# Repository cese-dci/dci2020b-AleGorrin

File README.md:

Prototipo Replica Adafruit HUZZAH32 - ESP32 Feather
TP Alejandro Gorrin
Diseno de Circuitos Impresos
11 Co Especializacion de sistemas embebidos

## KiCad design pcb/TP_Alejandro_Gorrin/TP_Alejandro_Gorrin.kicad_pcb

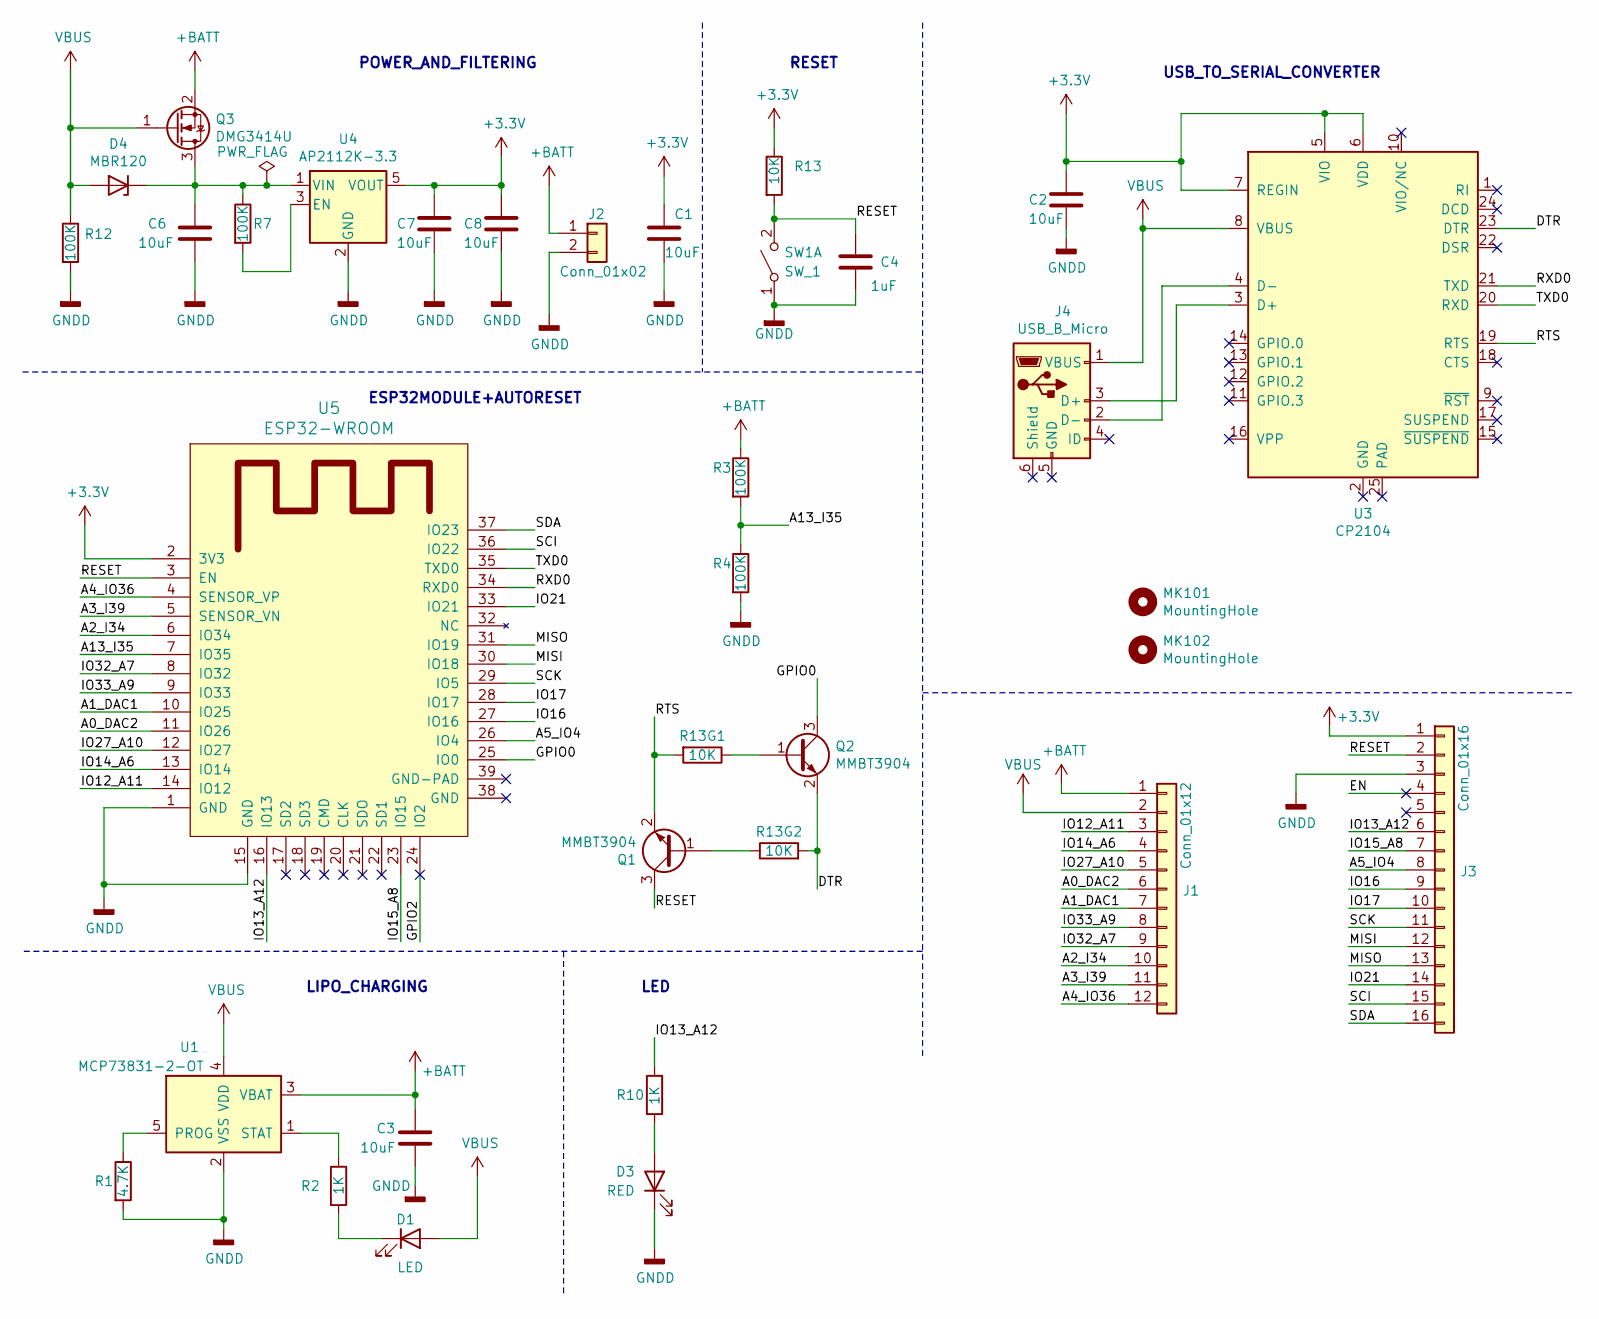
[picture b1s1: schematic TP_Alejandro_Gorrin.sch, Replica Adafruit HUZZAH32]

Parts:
C1, C2, C3, C6, C7, C8: 10uF; C_0805_2012Metric
C4: 1uF; C_0805_2012Metric
D1: LED; LED_0805_2012Metric
D3: RED; LED_0805_2012Metric
D4: MBR120; LED_0805_2012Metric
J1: Conn_01x12; PinHeader_1x12_P2.54mm_Vertical
J2: Conn_01x02; PinHeader_1x02_P2.54mm_Vertical
J3: Conn_01x16; PinHeader_1x16_P2.54mm_Vertical
J4: USB_B_Micro; USB_Micro-B_Molex_47346-0001
MK101, MK102: MountingHole; MountingHole_2.2mm_M2_DIN965_Pad
Q1, Q2: MMBT3904; SOT-23
Q3: DMG3414U; SOT-23
R1: 4.7K; R_0805_2012Metric
R2, R10: 1K; R_0805_2012Metric
R3, R4, R7, R12: 100K; R_0805_2012Metric
R13, R13G1, R13G2: 10K; R_0805_2012Metric
SW1: SW_1; SW_Push_1P1T_NO_6x6mm_H9.5mm
U1: MCP73831-2-OT; SOT-23-5
U3: CP2104; QFN-24-1EP_4x4mm_P0.5mm_EP2.6x2.6mm
U4: AP2112K-3.3; SOT-23-5
U5: ESP32-WROOM

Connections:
+3V3: C1.1, C2.1, C7.1, C8.1, J3.1, R13.1, U3.5 (VIO), U3.6 (VDD), U3.7 (REGIN), U4.5 (VOUT), U5.2 (3V3)
+BATT: C3.2, J1.1, J2.1, Q3.2 (S), R3.1, U1.3 (VBAT)
/A0_DAC2: J1.6, U5.11 (IO26)
/A1_DAC1: J1.7, U5.10 (IO25)
/A2_I34: J1.10, U5.6 (IO34)
/A3_I39: J1.11, U5.5 (SENSOR_VN)
/A4_IO36: J1.12, U5.4 (SENSOR_VP)
/A5_IO4: J3.8, U5.26 (IO4)
/A13_I35: R3.2, R4.1, U5.7 (IO35)
/DTR: Q2.2 (E), R13G2.2, U3.23 (DTR)
/EN: J3.4
/GPIO0: Q2.3 (C), U5.25 (IO0)
/GPIO2: U5.24 (IO2)
/IO12_A11: J1.3, U5.14 (IO12)
/IO13_A12: J3.6, R10.2, U5.16 (IO13)
/IO14_A6: J1.4, U5.13 (IO14)
/IO15_A8: J3.7, U5.23 (IO15)
/IO16: J3.9, U5.27 (IO16)
/IO17: J3.10, U5.28 (IO17)
/IO21: J3.14, U5.33 (IO21)
/IO27_A10: J1.5, U5.12 (IO27)
/IO32_A7: J1.9, U5.8 (IO32)
/IO33_A9: J1.8, U5.9 (IO33)
/MISI: J3.12, U5.30 (IO18)
/MISO: J3.13, U5.31 (IO19)
/RESET: C4.1, J3.2, Q1.3 (C), R13.2, SW1.2 (B), U5.3 (EN)
/RTS: Q1.2 (E), R13G1.2, U3.19 (RTS)
/RXD0: U3.21 (TXD), U5.34 (RXD0)
/SCI: J3.15, U5.36 (IO22)
/SCK: J3.11, U5.29 (IO5)
/SDA: J3.16, U5.37 (IO23)
/TXD0: U3.20 (RXD), U5.35 (TXD0)
GNDD: C1.2, C2.2, C3.1, C4.2, C6.2, C7.2, C8.2, D3.1 (K), J2.2, J3.3, J4.5 (GND), R1.2, R4.2, R12.2, SW1.1 (A), U1.2 (VSS), U4.2 (GND), U5.1 (GND), U5.15 (GND)
unnamed: C6.1, D4.1 (K), Q3.3 (D), R7.1, U4.1 (VIN)
unnamed: D1.1 (K), R2.2
unnamed: D3.2 (A), R10.1
unnamed: J4.2 (D-), U3.4 (D-)
unnamed: J4.3 (D+), U3.3 (D+)
unnamed: Q1.1 (B), R13G2.1
unnamed: Q2.1 (B), R13G1.1
unnamed: R1.1, U1.5 (PROG)
unnamed: R2.1, U1.1 (STAT)
unnamed: R7.2, U4.3 (EN)
VBUS: D1.2 (A), D4.2 (A), J1.2, J4.1 (VBUS), Q3.1 (G), R12.1, U1.4 (VDD), U3.8 (VBUS)

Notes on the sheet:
LIPO_CHARGING
LED
ESP32MODULE+AUTORESET
USB_TO_SERIAL_CONVERTER
RESET
POWER_AND_FILTERING

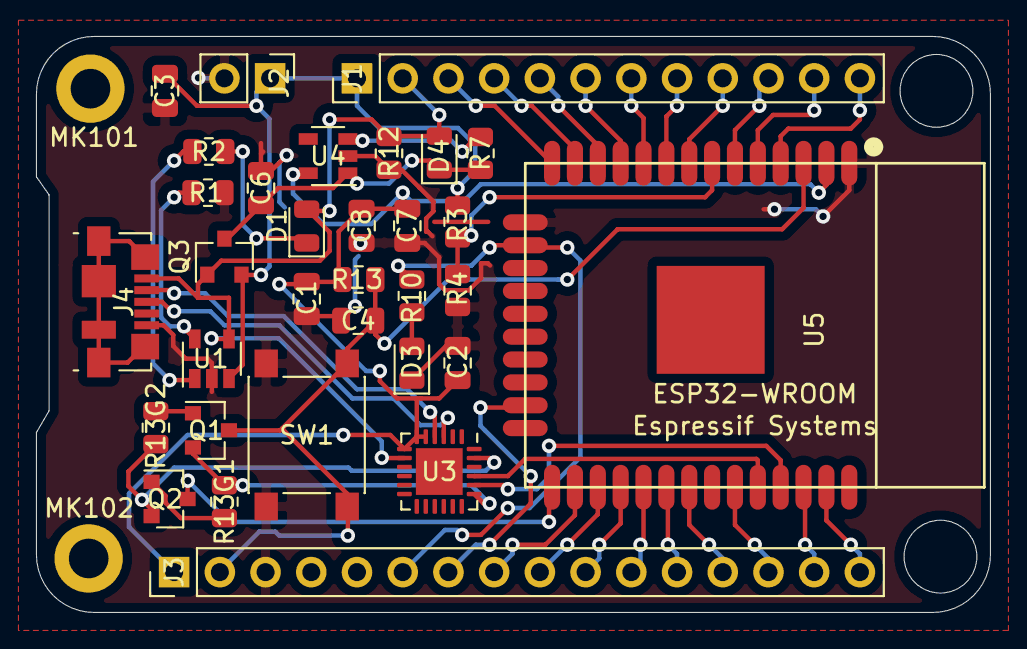
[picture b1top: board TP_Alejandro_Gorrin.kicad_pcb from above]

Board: 2 copper layers, 53.0 x 32.0 mm, 34 parts (0 on the bottom side), 42 nets.

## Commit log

2020-10-10 commit inicial
2020-10-10 cambio terminales
2020-10-10 cambio de nombre al compilar
2020-10-11 cambio de componente
2020-10-11 asignacion de footprint
2020-10-14 Agrego PWR FLAGS
2020-10-14 footprint y componente ESP32
2020-10-14 readme
2020-10-14 Empezando con el ruteo
2020-10-15 vias del PCB
2020-10-22 Cambios del Esquematico
2020-11-02 Agrego avances de PCB, problemas con el heatsink
2020-11-02 Cambios PCB
2020-11-06 Avances PCB
2020-11-07 PCB conexiones realizadas
2020-11-08 Cambio y agrego vias para facilitar el ruteo
2020-11-08 Se observa problema con GNDD
2020-11-16 PCB cambios

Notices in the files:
pcb/TP_Alejandro_Gorrin/TP_Alejandro_Gorrin.kicad_pcb:
Licencia: CC BY-NC-CA
